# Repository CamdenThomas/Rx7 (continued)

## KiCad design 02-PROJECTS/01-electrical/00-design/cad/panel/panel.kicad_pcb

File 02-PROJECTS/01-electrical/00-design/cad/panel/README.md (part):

# Control panel — the KiCad project

*Rev 2026-10-13 (sheet and board rev 0.04, provisional - Y20, D-492) · owns: what this KiCad project
is for and what it may claim. The panel's design is `../../../data/panel_ribbon.csv`, the cavities of
`DP-DCU-E`, `dcu_channels` SN17-SN20 and parts P155, P192, P201 (D-492, D-458, D-459). Read
`../README.md` first: it is the fence.*

## Where it stands

**Rev 0.04 is the sketch's control set (D-492)**, drawn in place of Y6's board (D-380's nine keys,
four encoders and the thumbstick, superseded). It is the face of the climate unit (D-479, D-481):
the board stands 8 mm behind the faceplate, inside the unit's enclosure, the DCU carrier behind it.

- **Schematic: ERC 0 errors, 0 warnings.** `../check.py --board panel`: 79 checks, 0 mismatches
  against `panel_ribbon` (every conductor, the keys on each row and column through their diodes,
  the encoders, the spares), against `DP-DCU-E` (the plate header pin for pin) and against the
  IS31FL3236A pin table.
- **Board: DRC 0 violations, 0 unconnected, 0 schematic-parity issues** with `--severity-all`.
  180 × 84.76 mm, 2 layers, 56 footprints (52 parts and four M3 holes), 0.25 mm tracks throughout
  (0.2 mm clearance, 0.6 / 0.3 mm vias), about 1660 segments and 110 vias, a GND pour on both layers
  with solid pad connections. Routed by a script (a grid router written for this board, no
  freerouting on this machine), so it is correct, not pretty: `H-008` lays out the final board.
- No processor, no CAN node, no 12 V (D-355): the ribbon's +5 V and I²C feed the lights and the screen.
- The thumbstick, the hatch and fuel-door keys are not on this board any more: they are on the
  left plate (Y21) and reach the ribbon through `J3` (below).

## The board, as seen from the faceplate

Millimetres from the board's top-left corner, x to the right, y down. **The outline is the mock-up's,
`confirm`**: the face is 192 × 96.76 (D-481), the board the face less `PANEL_MARGIN` 6 a side
(`../climate-unit/unit_params.py`). The sketch's 180 × 60 control block is centred on the face, so
**board x = sketch x and board y = sketch y + 12.378**. Four M3 holes 4 mm in from the corners:
(4, 4), (176, 4), (4, 80.76), (176, 80.76).

| Control | Part | Board (x, y) | On the face (the sketch) |
|---|---|---|---|
| screen window | `J2` header for the module, pin 1 at (86.19, 12.0), pins along +x | window centre (90, 27.38) | 44 × 23.6 window |
| centre knob | `SW7` encoder with push | (90, 54.38) | Ø20 knob |
| fan-mode key (upper left) | `SW2` | (67.7, 48.88) | 13 × 8 cap |
| recirculate key (upper right) | `SW3` | (112.3, 48.88) | 13 × 8 cap |
| rear-defog key (lower left) | `SW1` | (67.7, 59.88) | 13 × 8 cap |
| mirror-defog key (lower right) | `SW4` | (112.3, 59.88) | 13 × 8 cap |
| driver seat knob | `SW8` | (40, 42.38) | Ø22 knob |
| passenger seat knob | `SW9` | (140, 42.38) | Ø22 knob |
| driver window switch | `SW5` | (12, 42.38) | 12 × 24 slot |
| passenger window switch | `SW6` | (168, 42.38) | 12 × 24 slot |

Key positions are the cap's centre (the `SW_PUSH_6mm` footprint's origin is pad 1, 3.25 / 2.25 mm
up-left of it). The faceplate's cut-outs are drawn on `Cmts.User`. "Upper / lower, left / right"
follow I-001: driver side is the left.

**The back** carries the rest: the ribbon header **`J1`** (2 × 13, centre (157, 68.26), pin 1 at
the right end (172.24, 69.53), toward the carrier's J4 pin 1 - `PANEL_RIBBON_Z` 16.5 above the bottom
edge, 0.5 more than the mock-up's 16 so `J3` fits under it; the carrier's J4 is straight behind at
x ≈ 158.4, this one 1.4 mm left of that so its shroud clears the board's edge, `confirm`), the plate header **`J3`** (2 × 6, centre (150, 78.6), pin 1 at the
right (156.35, 79.87)), the light driver **`U2`** at (90.05, 30.05) behind the screen with **`C2`,
`C3`, `R1`, `R2`** under it, **`C1`** by `J1` pin 26, the eight matrix diodes beside their switches,
the screen-supply jumper **`JP1`** at (101, 12) and **`TP1`** (the ribbon's spare) at (128, 80.5).

## The ribbon, J1 (`panel_ribbon`, pin for pin)

| Pin | Net | On this board |
|---|---|---|
| 1 | `+3V3` | `J3` 7 only (the stick's pots, on the plate); `JP1` 3 if the screen is set to 3.3 V |
| 2, 21, 23 | `GND` | encoder commons, the centre push, `U2`, `C1`-`C3`, `R1`, the screen; 21 / 23 guard the I²C pair |
| 3 | `ROW1` | rear defog (`D1`); `J3` 1 for the plate's hatch and fuel-door keys |
| 4 | `ROW2` | HVAC mode (`D2`), recirculate (`D3`), window DRV up (`D4`) |
| 5 | `ROW3` | window DRV down (`D5`), PASS up (`D6`), PASS down (`D7`) |
| 6 | `COL1` | rear defog, HVAC mode, window DRV down, mirror defog |
| 7 | `COL2` | recirculate, window PASS up; `J3` 2 (hatch) |
| 8 | `COL3` | window DRV up, window PASS down; `J3` 3 (fuel door) |
| 9 / 10 | `ENC_CENTRE_A` / `_B` | `SW7` A / B |
| 11 | `ENC_CENTRE_PUSH` | `SW7` S1 (S2 to GND) |
| 12 | `ROW4` | mirror defog (`D8`); columns 2 and 3 spare |
| 13 / 14 | `ENC_SEAT_DRV_A` / `_B` | `SW8` A / B |
| 15 / 16 | `ENC_SEAT_PASS_A` / `_B` | `SW9` A / B |
| 17 / 18 / 19 | `JOY_X` / `JOY_Y` / `JOY_PRESS` | `J3` 4 / 5 / 6 only |
| 20 | `AGND` | `J3` 8 only - kept apart from `GND` on this board; they meet on the carrier |
| 22 / 24 | `PNL_SDA` / `PNL_SCL` | `U2`, the screen `J2`, `J3` 9 / 10 |
| 25 | `SPARE` | `TP1` |
| 26 | `+5V_PNL` | `U2` VCC, the 24 LED anodes, `C1`-`C3`, `R2`, `JP1` 1, `J3` 12 |

**The matrix:** one 1N4148W per key, cathode to the row, anode toward the column (a row driven low
pulls its column low; with every row held low any press wakes the DCU). Eight diodes on this board,
the plate's two keys carry their own (D-492).

**The window switches** are drawn as a centre-sprung **DPDT** (ON)-OFF-(ON) toggle, one pole per
direction. The record puts DRV up at `ROW2` / `COL3` and DRV down at `ROW3` / `COL1`: two different
rows *and* two different columns, which an SPDT's single common cannot serve without a phantom key
(its common would join two rows or two columns). With two poles each contact is an ordinary key
behind its own diode. PASS (both on `ROW3`) could use an SPDT, but both switches are the same part.
If the record re-pins DRV up / down onto one row or one column, an SPDT fits and P155 can stay as worded.

## The plate header, J3 - what the left plate (Y21) carries

`J3` is `DP-DCU-E` 1-12 pin for pin; a lead joins it to the upper connector board's `J8`, which runs
straight through to the DT13 `DP-DCU-E` in the unit's back wall and on to the plate's cable (P200).

| Pin | Net | panel_ribbon | On the plate |
|---|---|---|---|
| 1 | `ROW1` | 3 | the row for its two keys |
| 2 | `COL2` | 7 | the hatch key, through its own 1N4148W |
| 3 | `COL3` | 8 | the fuel-door key, through its own 1N4148W |
| 4 / 5 | `JOY_X` / `JOY_Y` | 17 / 18 | the mirror stick's wipers (P156) |
| 6 | `JOY_PRESS` | 19 | the stick's push, to GND |
| 7 | `+3V3` | 1 | the stick's pot supply |
| 8 | `AGND` | 20 | the stick's pot ground |
| 9 / 10 | `PNL_SDA` / `PNL_SCL` | 22 / 24 | the plate's own I²C LED driver (its symbols) |
| 11 | `GND` | 21 | the plate's lights and logic return |
| 12 | `+5V_PNL` | 26 | the plate's LED supply |

The two wink switches on the plate are not here: they stay hardwired to the PMU (DV24, D-492).

## The lights (D-458, D-492)

**`U2`, IS31FL3236A-TQLS4** (eTQFP-48, I²C **0x3C**, AD to GND), as on Y6: `C1` 10 µF at `J1` 26,
`C2` 1 µF and `C3` 100 nF at VCC, `R1` 10 k on R_EXT (IMAX = 58.5 × 1.3 V / 10 k = 7.6 mA a channel,
p.11), `R2` 100 k holding SDB high (on and blank until written). 24 LEDs, 0603, anode on `+5V_PNL`,
cathode to the channel - 24 × 7.6 mA = 0.18 A at full current. The fan and temperature arcs of D-458
are gone; the screen shows those. Which lights follow the headlights (the ring, the window and seat
symbols) and which show state (the key symbols, the seat arcs) is firmware's (I-004), not wiring.

The channel map was chosen from the geometry (channels taken round `U2` in the same order as the
LEDs around it, so the runs do not cross); the record names no order. **F-018 reads it from here.**

| OUT | LED | What it lights | x | y |
|---|---|---|---|---|
| 3 | `LED8` | knob ring, lower left | 80.454 | 63.924 |
| 5 | `LED1` | rear-defog key symbol | 73.3 | 59.878 |
| 6 | `LED5` | knob ring, upper left | 80.454 | 44.832 |
| 7 | `LED2` | fan-mode key symbol | 73.3 | 48.878 |
| 9 | `LED18` | driver seat heat 3 | 54.943 | 43.685 |
| 10 | `LED13` | driver seat cool 3 | 25.057 | 43.685 |
| 11 | `LED17` | driver seat heat 2 | 54.095 | 37.248 |
| 13 | `LED14` | driver seat cool 2 | 25.905 | 37.248 |
| 14 | `LED16` | driver seat heat 1 | 50.607 | 31.771 |
| 15 | `LED9` | driver window symbol | 12.0 | 32.978 |
| 17 | `LED15` | driver seat cool 1 | 29.393 | 31.771 |
| 18 | `LED11` | driver seat symbol | 40.0 | 27.978 |
| 19 | `LED12` | passenger seat symbol | 140.0 | 27.978 |
| 21 | `LED22` | passenger seat heat 1 | 150.607 | 31.771 |
| 22 | `LED10` | passenger window symbol | 168.0 | 32.978 |
| 23 | `LED21` | passenger seat cool 1 | 129.393 | 31.771 |
| 25 | `LED23` | passenger seat heat 2 | 154.095 | 37.248 |
| 26 | `LED20` | passenger seat cool 2 | 125.905 | 37.248 |
| 27 | `LED24` | passenger seat heat 3 | 154.943 | 43.685 |
| 29 | `LED19` | passenger seat cool 3 | 125.057 | 43.685 |
| 30 | `LED3` | recirculate key symbol | 106.7 | 48.878 |
| 31 | `LED6` | knob ring, upper right | 99.546 | 44.832 |
| 33 | `LED4` | mirror-defog key symbol | 106.7 | 59.878 |
| 34 | `LED7` | knob ring, lower right | 99.546 | 63.924 |

OUT 1, 2, 4, 8, 12, 16, 20, 24, 28, 32, 35 and 36 are open. The (x, y) are the faceplate's windows
for LP20, from the board's top-left as seen from the face.

- **Key symbols** sit inside the 13 × 8 cap, beside the tactile switch on the knob's side (5.6 mm from
  the cap's centre; the switch fills the middle), lit through the cap (D-488).
- **The knob's ring:** four LEDs on the diagonals, 13.5 mm from the shaft, toward the four keys (I-001).
- **Seat arcs:** 15 mm from the shaft, OFF at the top (D-073); cool 3-2-1 anticlockwise at −95°, −70°,
  −45° (blue), heat 1-2-3 clockwise at +45°, +70°, +95° (red), the same on both knobs.
- **Window symbols** 9.4 mm above the switch, inside its 12 × 24 slot; **seat symbols** 14.4 mm above
  the knob's shaft. I-005 asks for the window symbol on the switch's cap and the seat symbol in the
  knob's centre: both are part questions (below), so the LED sits beside the control for now.

## The screen (P201)

`J2` is a placeholder for a 128 × 64-class I²C module's own 4-pin header, in the common order
**GND, VCC, SCL, SDA**, centred over the window's top edge (a 1.3-inch module's header sits there).
**`JP1` picks its supply and is left open**: bridge 1-2 for `+5V_PNL` (what the record allows - its
`+3V3` line says "nothing else on the panel is powered from it"), or 2-3 for `+3V3`. Many modules pull
SDA / SCL up to their VCC pin: such a module at 5 V would pull the DCU's 3.3 V bus to 5 V, which the
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
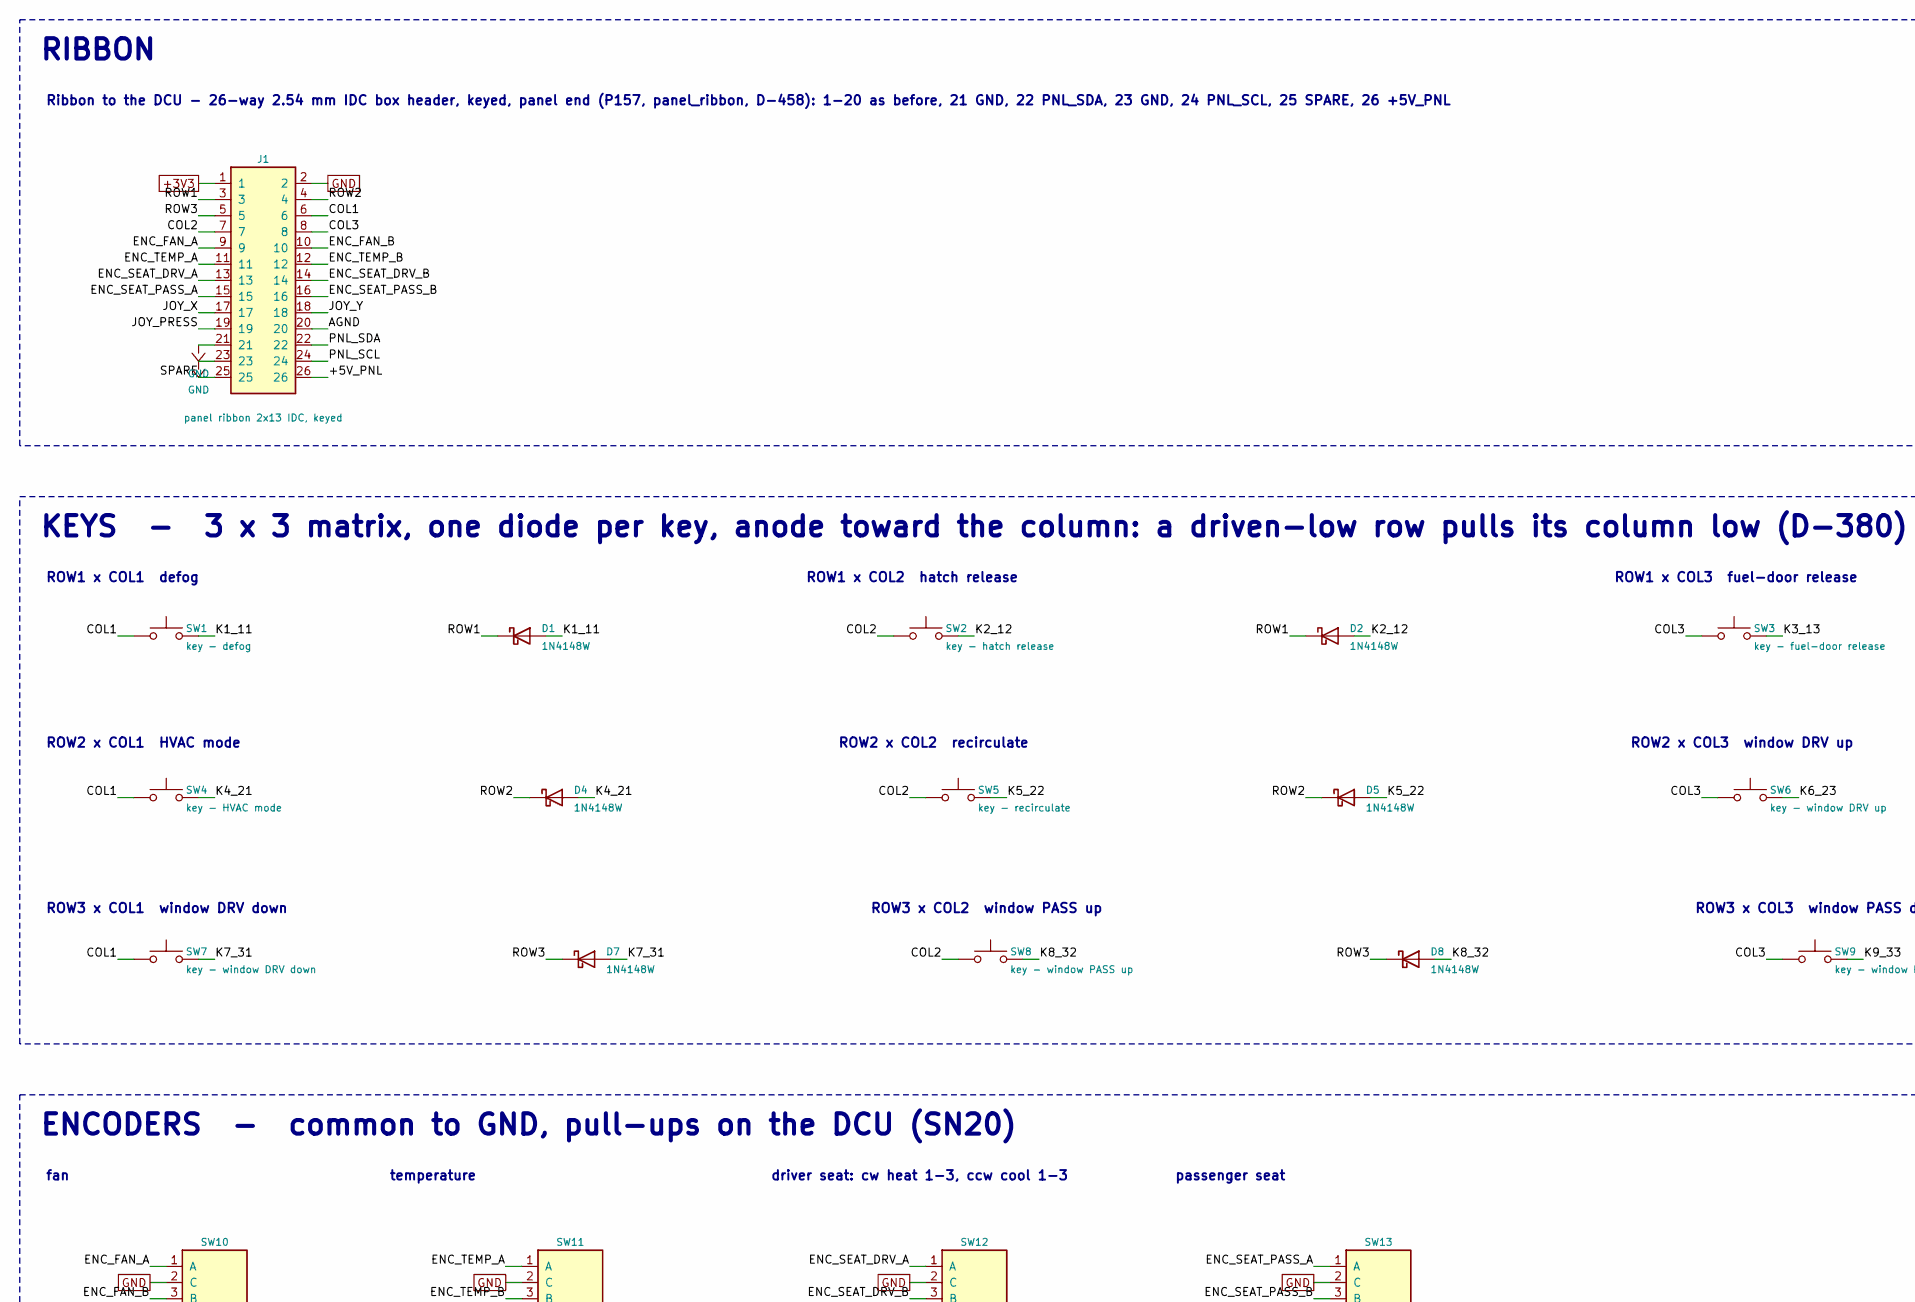
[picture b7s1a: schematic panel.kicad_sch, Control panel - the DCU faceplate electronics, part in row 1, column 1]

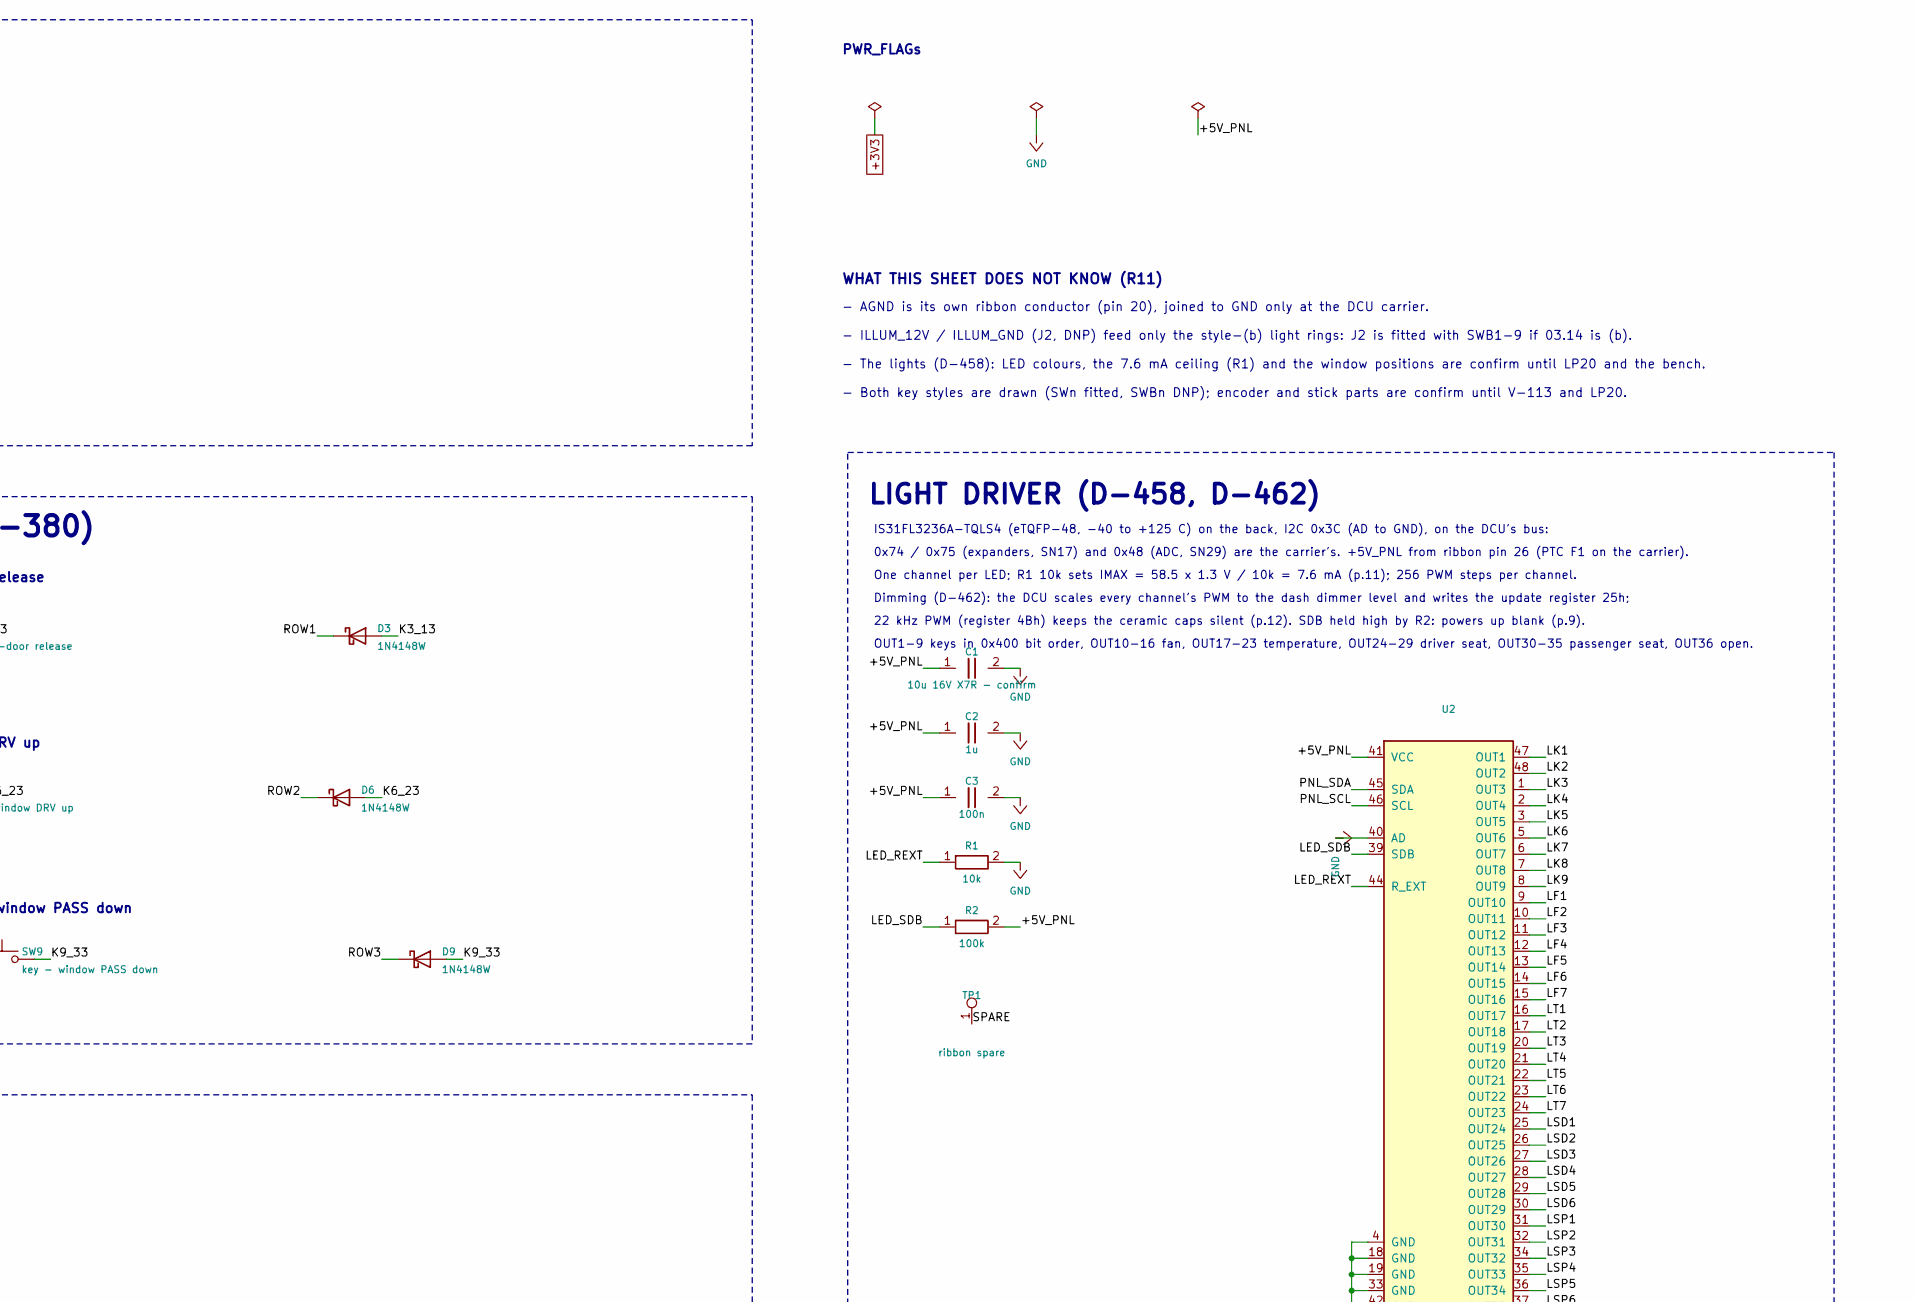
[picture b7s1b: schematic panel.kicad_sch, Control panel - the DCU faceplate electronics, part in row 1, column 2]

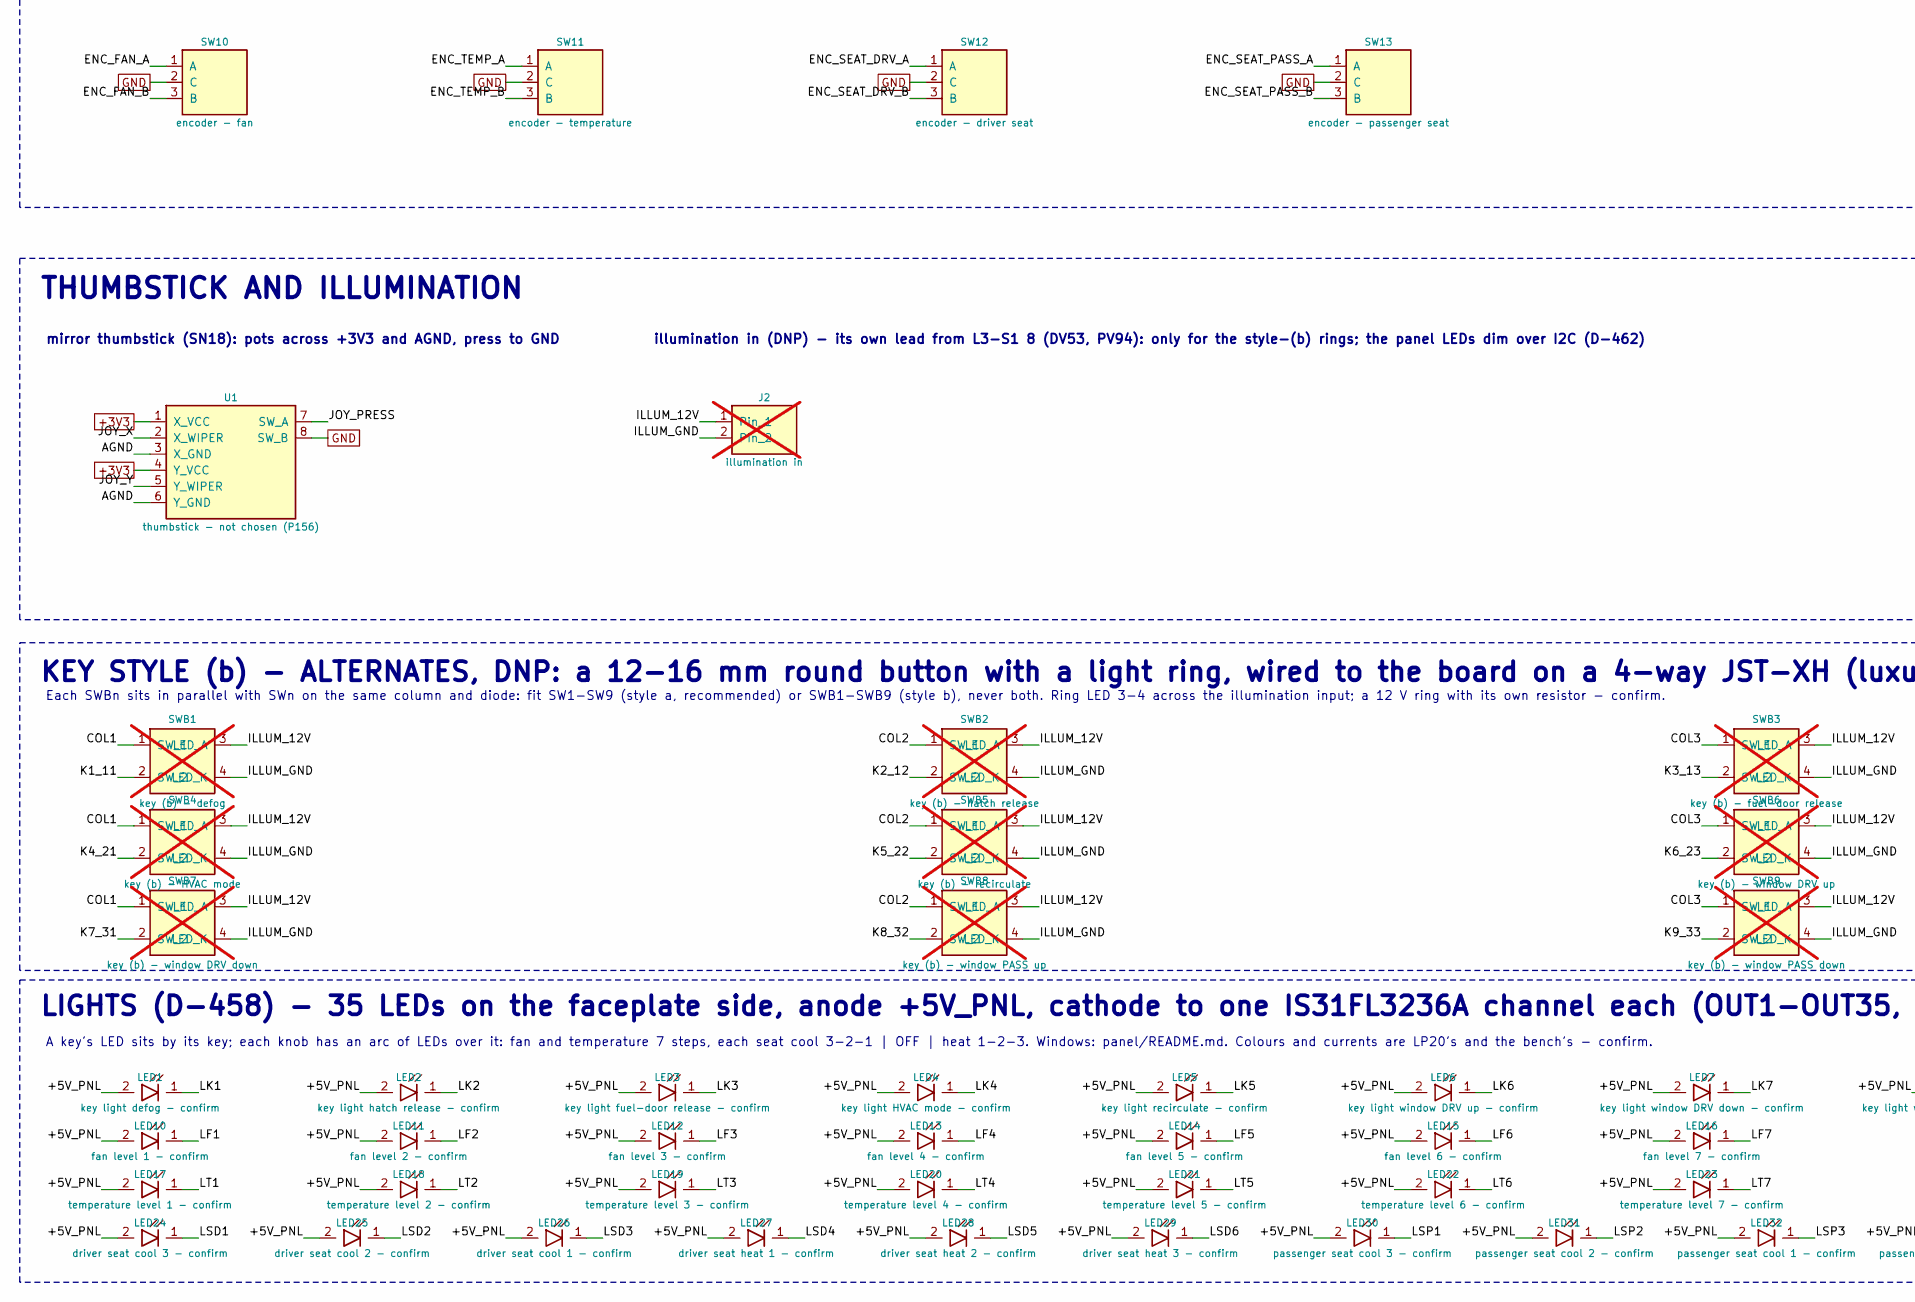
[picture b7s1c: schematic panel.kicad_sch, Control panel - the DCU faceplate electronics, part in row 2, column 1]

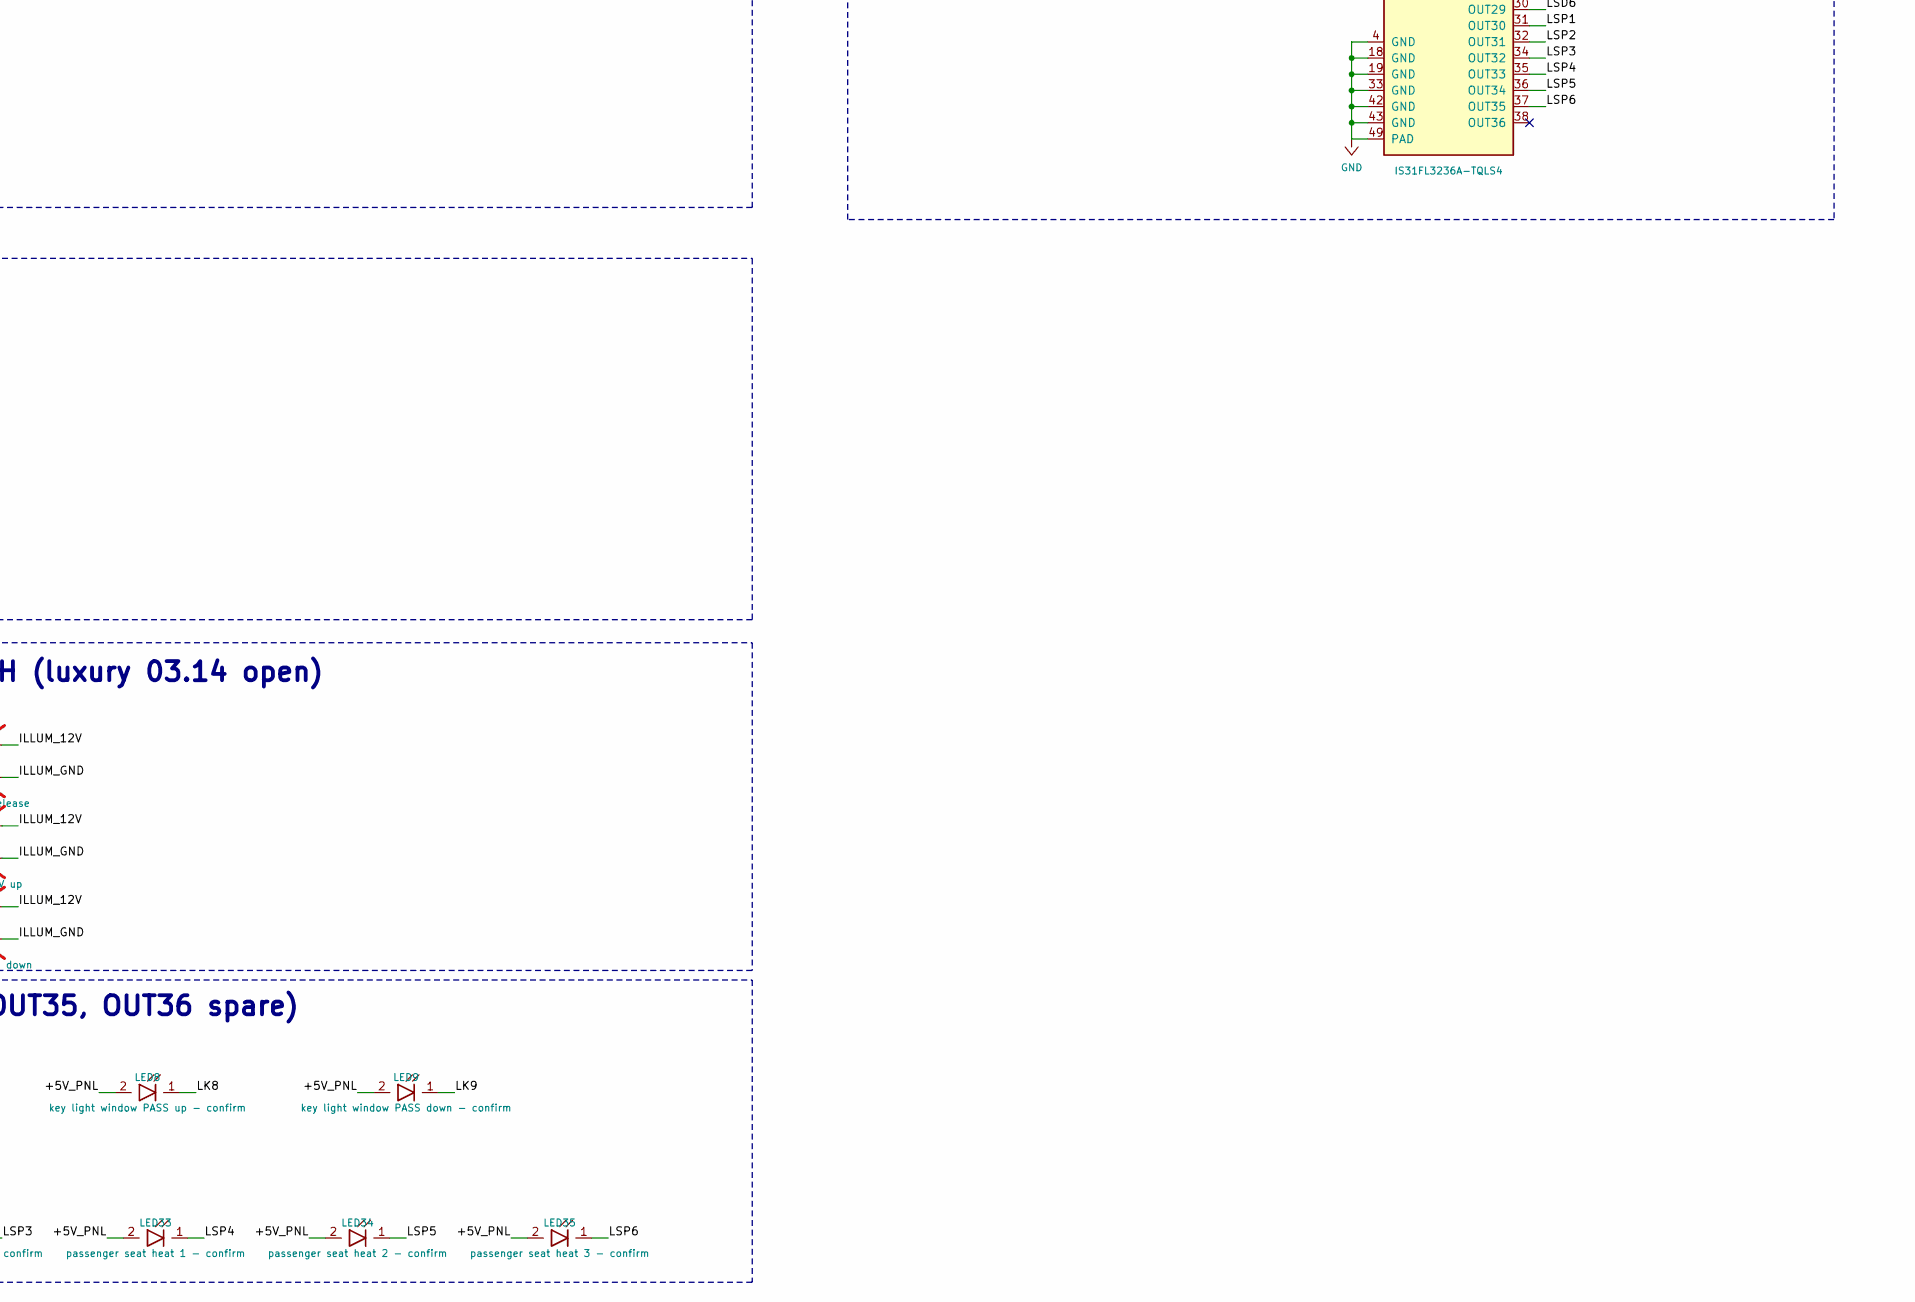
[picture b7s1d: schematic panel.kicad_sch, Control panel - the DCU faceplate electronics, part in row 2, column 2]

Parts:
C1: 10u 16V X7R - confirm; C_0805_2012Metric
C2: 1u; C_0603_1608Metric
C3: 100n; C_0603_1608Metric
D1, D2, D3, D4, D5, D6, D7, D8, D9: 1N4148W; D_SOD-123
J1: panel ribbon 2x13 IDC, keyed; IDC-Header_2x13_P2.54mm_Vertical
J2: illumination in; JST_XH_B2B-XH-A_1x02_P2.50mm_Vertical; not fitted
LED1: key light defog - confirm; LED_1206_3216Metric
LED2: key light hatch release - confirm; LED_1206_3216Metric
LED3: key light fuel-door release - confirm; LED_1206_3216Metric
LED4: key light HVAC mode - confirm; LED_1206_3216Metric
LED5: key light recirculate - confirm; LED_1206_3216Metric
LED6: key light window DRV up - confirm; LED_1206_3216Metric
LED7: key light window DRV down - confirm; LED_1206_3216Metric
LED8: key light window PASS up - confirm; LED_1206_3216Metric
LED9: key light window PASS down - confirm; LED_1206_3216Metric
LED10: fan level 1 - confirm; LED_0603_1608Metric
LED11: fan level 2 - confirm; LED_0603_1608Metric
LED12: fan level 3 - confirm; LED_0603_1608Metric
LED13: fan level 4 - confirm; LED_0603_1608Metric
LED14: fan level 5 - confirm; LED_0603_1608Metric
LED15: fan level 6 - confirm; LED_0603_1608Metric
LED16: fan level 7 - confirm; LED_0603_1608Metric
LED17: temperature level 1 - confirm; LED_0603_1608Metric
LED18: temperature level 2 - confirm; LED_0603_1608Metric
LED19: temperature level 3 - confirm; LED_0603_1608Metric
LED20: temperature level 4 - confirm; LED_0603_1608Metric
LED21: temperature level 5 - confirm; LED_0603_1608Metric
LED22: temperature level 6 - confirm; LED_0603_1608Metric
LED23: temperature level 7 - confirm; LED_0603_1608Metric
LED24: driver seat cool 3 - confirm; LED_0603_1608Metric
LED25: driver seat cool 2 - confirm; LED_0603_1608Metric
LED26: driver seat cool 1 - confirm; LED_0603_1608Metric
LED27: driver seat heat 1 - confirm; LED_0603_1608Metric
LED28: driver seat heat 2 - confirm; LED_0603_1608Metric
LED29: driver seat heat 3 - confirm; LED_0603_1608Metric
LED30: passenger seat cool 3 - confirm; LED_0603_1608Metric
LED31: passenger seat cool 2 - confirm; LED_0603_1608Metric
LED32: passenger seat cool 1 - confirm; LED_0603_1608Metric
LED33: passenger seat heat 1 - confirm; LED_0603_1608Metric
LED34: passenger seat heat 2 - confirm; LED_0603_1608Metric
LED35: passenger seat heat 3 - confirm; LED_0603_1608Metric
R1: 10k; R_0603_1608Metric
R2: 100k; R_0603_1608Metric
SW1: key - defog; SW_PUSH_6mm_H13mm
SW2: key - hatch release; SW_PUSH_6mm_H13mm
SW3: key - fuel-door release; SW_PUSH_6mm_H13mm
SW4: key - HVAC mode; SW_PUSH_6mm_H13mm
SW5: key - recirculate; SW_PUSH_6mm_H13mm
SW6: key - window DRV up; SW_PUSH_6mm_H13mm
SW7: key - window DRV down; SW_PUSH_6mm_H13mm
SW8: key - window PASS up; SW_PUSH_6mm_H13mm
SW9: key - window PASS down; SW_PUSH_6mm_H13mm
SW10: encoder - fan; RotaryEncoder_Bourns_Vertical_PEC11R-4xxxF-Sxxxx
SW11: encoder - temperature; RotaryEncoder_Bourns_Vertical_PEC11R-4xxxF-Sxxxx
SW12: encoder - driver seat; RotaryEncoder_Bourns_Vertical_PEC11R-4xxxF-Sxxxx
SW13: encoder - passenger seat; RotaryEncoder_Bourns_Vertical_PEC11R-4xxxF-Sxxxx
SWB1: key (b) - defog; JST_XH_B4B-XH-A_1x04_P2.50mm_Vertical; not fitted
SWB2: key (b) - hatch release; JST_XH_B4B-XH-A_1x04_P2.50mm_Vertical; not fitted
SWB3: key (b) - fuel-door release; JST_XH_B4B-XH-A_1x04_P2.50mm_Vertical; not fitted
SWB4: key (b) - HVAC mode; JST_XH_B4B-XH-A_1x04_P2.50mm_Vertical; not fitted
SWB5: key (b) - recirculate; JST_XH_B4B-XH-A_1x04_P2.50mm_Vertical; not fitted
SWB6: key (b) - window DRV up; JST_XH_B4B-XH-A_1x04_P2.50mm_Vertical; not fitted
SWB7: key (b) - window DRV down; JST_XH_B4B-XH-A_1x04_P2.50mm_Vertical; not fitted
SWB8: key (b) - window PASS up; JST_XH_B4B-XH-A_1x04_P2.50mm_Vertical; not fitted
SWB9: key (b) - window PASS down; JST_XH_B4B-XH-A_1x04_P2.50mm_Vertical; not fitted
TP1: ribbon spare; TestPoint_Pad_D1.5mm
U1: thumbstick - not chosen (P156); Thumbstick_P156_Placeholder_2x04_P2.54mm
U2: IS31FL3236A-TQLS4; TQFP-48-1EP_7x7mm_P0.5mm_EP4.11x4.11mm

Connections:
+3V3: J1.1, U1.1 (X_VCC), U1.4 (Y_VCC)
/+5V_PNL: C1.1, C2.1, C3.1, J1.26, LED1.2 (A), LED2.2 (A), LED3.2 (A), LED4.2 (A), LED5.2 (A), LED6.2 (A), LED7.2 (A), LED8.2 (A), LED9.2 (A), LED10.2 (A), LED11.2 (A), LED12.2 (A), LED13.2 (A), LED14.2 (A), LED15.2 (A), LED16.2 (A), LED17.2 (A), LED18.2 (A), LED19.2 (A), LED20.2 (A), LED21.2 (A), LED22.2 (A), LED23.2 (A), LED24.2 (A), LED25.2 (A), LED26.2 (A), LED27.2 (A), LED28.2 (A), LED29.2 (A), LED30.2 (A), LED31.2 (A), LED32.2 (A), LED33.2 (A), LED34.2 (A), LED35.2 (A), R2.2, U2.41 (VCC)
/AGND: J1.20, U1.3 (X_GND), U1.6 (Y_GND)
/COL1: J1.6, SW1.1, SW4.1, SW7.1, SWB1.1 (SW_1), SWB4.1 (SW_1), SWB7.1 (SW_1)
/COL2: J1.7, SW2.1, SW5.1, SW8.1, SWB2.1 (SW_1), SWB5.1 (SW_1), SWB8.1 (SW_1)
/COL3: J1.8, SW3.1, SW6.1, SW9.1, SWB3.1 (SW_1), SWB6.1 (SW_1), SWB9.1 (SW_1)
/ENC_FAN_A: J1.9, SW10.1 (A)
/ENC_FAN_B: J1.10, SW10.3 (B)
/ENC_SEAT_DRV_A: J1.13, SW12.1 (A)
/ENC_SEAT_DRV_B: J1.14, SW12.3 (B)
/ENC_SEAT_PASS_A: J1.15, SW13.1 (A)
/ENC_SEAT_PASS_B: J1.16, SW13.3 (B)
/ENC_TEMP_A: J1.11, SW11.1 (A)
/ENC_TEMP_B: J1.12, SW11.3 (B)
/ILLUM_12V: J2.1, SWB1.3 (LED_A), SWB2.3 (LED_A), SWB3.3 (LED_A), SWB4.3 (LED_A), SWB5.3 (LED_A), SWB6.3 (LED_A), SWB7.3 (LED_A), SWB8.3 (LED_A), SWB9.3 (LED_A)
/ILLUM_GND: J2.2, SWB1.4 (LED_K), SWB2.4 (LED_K), SWB3.4 (LED_K), SWB4.4 (LED_K), SWB5.4 (LED_K), SWB6.4 (LED_K), SWB7.4 (LED_K), SWB8.4 (LED_K), SWB9.4 (LED_K)
/JOY_PRESS: J1.19, U1.7 (SW_A)
/JOY_X: J1.17, U1.2 (X_WIPER)
/JOY_Y: J1.18, U1.5 (Y_WIPER)
/K1_11: D1.2 (A), SW1.2, SWB1.2 (SW_2)
/K2_12: D2.2 (A), SW2.2, SWB2.2 (SW_2)
/K3_13: D3.2 (A), SW3.2, SWB3.2 (SW_2)
/K4_21: D4.2 (A), SW4.2, SWB4.2 (SW_2)
/K5_22: D5.2 (A), SW5.2, SWB5.2 (SW_2)
/K6_23: D6.2 (A), SW6.2, SWB6.2 (SW_2)
/K7_31: D7.2 (A), SW7.2, SWB7.2 (SW_2)
/K8_32: D8.2 (A), SW8.2, SWB8.2 (SW_2)
/K9_33: D9.2 (A), SW9.2, SWB9.2 (SW_2)
/LED_REXT: R1.1, U2.44 (R_EXT)
/LED_SDB: R2.1, U2.39 (SDB)
/LF1: LED10.1 (K), U2.9 (OUT10)
/LF2: LED11.1 (K), U2.10 (OUT11)
/LF3: LED12.1 (K), U2.11 (OUT12)
/LF4: LED13.1 (K), U2.12 (OUT13)
/LF5: LED14.1 (K), U2.13 (OUT14)
/LF6: LED15.1 (K), U2.14 (OUT15)
/LF7: LED16.1 (K), U2.15 (OUT16)
/LK1: LED1.1 (K), U2.47 (OUT1)
/LK2: LED2.1 (K), U2.48 (OUT2)
/LK3: LED3.1 (K), U2.1 (OUT3)
/LK4: LED4.1 (K), U2.2 (OUT4)
/LK5: LED5.1 (K), U2.3 (OUT5)
/LK6: LED6.1 (K), U2.5 (OUT6)
/LK7: LED7.1 (K), U2.6 (OUT7)
/LK8: LED8.1 (K), U2.7 (OUT8)
/LK9: LED9.1 (K), U2.8 (OUT9)
/LSD1: LED24.1 (K), U2.25 (OUT24)
/LSD2: LED25.1 (K), U2.26 (OUT25)
/LSD3: LED26.1 (K), U2.27 (OUT26)
/LSD4: LED27.1 (K), U2.28 (OUT27)
/LSD5: LED28.1 (K), U2.29 (OUT28)
/LSD6: LED29.1 (K), U2.30 (OUT29)
/LSP1: LED30.1 (K), U2.31 (OUT30)
/LSP2: LED31.1 (K), U2.32 (OUT31)
/LSP3: LED32.1 (K), U2.34 (OUT32)
/LSP4: LED33.1 (K), U2.35 (OUT33)
/LSP5: LED34.1 (K), U2.36 (OUT34)
/LSP6: LED35.1 (K), U2.37 (OUT35)
/LT1: LED17.1 (K), U2.16 (OUT17)
/LT2: LED18.1 (K), U2.17 (OUT18)
/LT3: LED19.1 (K), U2.20 (OUT19)
/LT4: LED20.1 (K), U2.21 (OUT20)
/LT5: LED21.1 (K), U2.22 (OUT21)
/LT6: LED22.1 (K), U2.23 (OUT22)
/LT7: LED23.1 (K), U2.24 (OUT23)
/PNL_SCL: J1.24, U2.46 (SCL)
/PNL_SDA: J1.22, U2.45 (SDA)
/ROW1: D1.1 (K), D2.1 (K), D3.1 (K), J1.3
/ROW2: D4.1 (K), D5.1 (K), D6.1 (K), J1.4
/ROW3: D7.1 (K), D8.1 (K), D9.1 (K), J1.5
/SPARE: J1.25, TP1.1
GND: C1.2, C2.2, C3.2, J1.2, J1.21, J1.23, R1.2, SW10.2 (C), SW11.2 (C), SW12.2 (C), SW13.2 (C), U1.8 (SW_B), U2.4 (GND), U2.18 (GND), U2.19 (GND), U2.33 (GND), U2.40 (AD), U2.42 (GND), U2.43 (GND), U2.49 (PAD)

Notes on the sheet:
RIBBON
Ribbon to the DCU - 26-way 2.54 mm IDC box header, keyed, panel end (P157, panel_ribbon, D-458): 1-20 as before, 21 GND, 22 PNL_SDA, 23 GND, 24 PNL_SCL, 25 SPARE, 26 +5V_PNL
KEYS - 3 x 3 matrix, one diode per key, anode toward the column: a driven-low row pulls its column low (D-380)
ROW1 x COL1 defog
ROW1 x COL2 hatch release
ROW1 x COL3 fuel-door release
ROW2 x COL1 HVAC mode
ROW2 x COL2 recirculate
ROW2 x COL3 window DRV up
ROW3 x COL1 window DRV down
ROW3 x COL2 window PASS up
ROW3 x COL3 window PASS down
ENCODERS - common to GND, pull-ups on the DCU (SN20)
fan
temperature
driver seat: cw heat 1-3, ccw cool 1-3
passenger seat
THUMBSTICK AND ILLUMINATION
mirror thumbstick (SN18): pots across +3V3 and AGND, press to GND
illumination in (DNP) - its own lead from L3-S1 8 (DV53, PV94): only for the style-(b) rings; the panel LEDs dim over I2C (D-462)
PWR_FLAGs
WHAT THIS SHEET DOES NOT KNOW (R11)
- AGND is its own ribbon conductor (pin 20), joined to GND only at the DCU carrier.
- ILLUM_12V / ILLUM_GND (J2, DNP) feed only the style-(b) light rings: J2 is fitted with SWB1-9 if 03.14 is (b).
- The lights (D-458): LED colours, the 7.6 mA ceiling (R1) and the window positions are confirm until LP20 and the bench.
- Both key styles are drawn (SWn fitted, SWBn DNP); encoder and stick parts are confirm until V-113 and LP20.
KEY STYLE (b) - ALTERNATES, DNP: a 12-16 mm round button with a light ring, wired to the board on a 4-way JST-XH (luxury 03.14 open)
Each SWBn sits in parallel with SWn on the same column and diode: fit SW1-SW9 (style a, recommended) or SWB1-SWB9 (style b), never both. Ring LED 3-4 across the illumination input; a 12 V ring with its own resistor - confirm.
LIGHTS (D-458) - 35 LEDs on the faceplate side, anode +5V_PNL, cathode to one IS31FL3236A channel each (OUT1-OUT35, OUT36 spare)
A key's LED sits by its key; each knob has an arc of LEDs over it: fan and temperature 7 steps, each seat cool 3-2-1 | OFF | heat 1-2-3. Windows: panel/README.md. Colours and currents are LP20's and the bench's - confirm.
LIGHT DRIVER (D-458, D-462)
IS31FL3236A-TQLS4 (eTQFP-48, -40 to +125 C) on the back, I2C 0x3C (AD to GND), on the DCU's bus:
0x74 / 0x75 (expanders, SN17) and 0x48 (ADC, SN29) are the carrier's. +5V_PNL from ribbon pin 26 (PTC F1 on the carrier).
One channel per LED; R1 10k sets IMAX = 58.5 x 1.3 V / 10k = 7.6 mA (p.11); 256 PWM steps per channel.
Dimming (D-462): the DCU scales every channel's PWM to the dash dimmer level and writes the update register 25h;
22 kHz PWM (register 4Bh) keeps the ceramic caps silent (p.12). SDB held high by R2: powers up blank (p.9).
OUT1-9 keys in 0x400 bit order, OUT10-16 fan, OUT17-23 temperature, OUT24-29 driver seat, OUT30-35 passenger seat, OUT36 open.

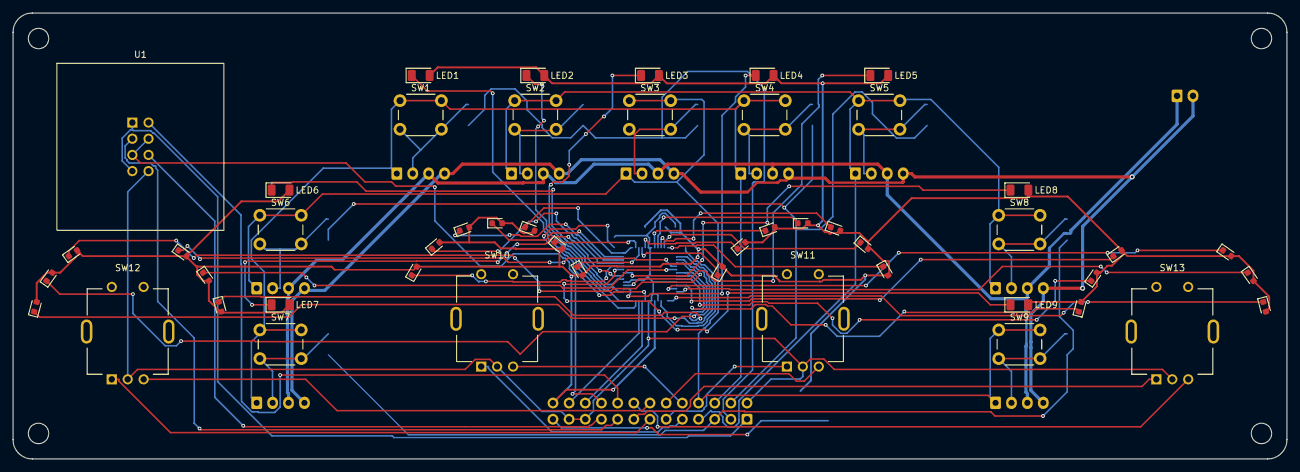
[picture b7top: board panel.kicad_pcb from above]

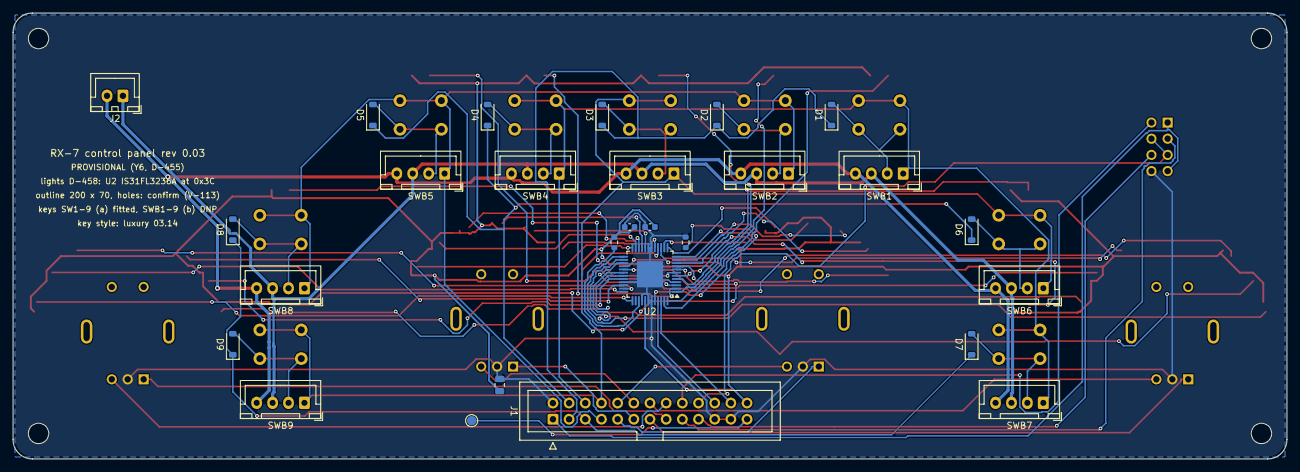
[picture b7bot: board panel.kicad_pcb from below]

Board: 2 copper layers, 200.0 x 70.0 mm, 80 parts (27 on the bottom side), 72 nets.

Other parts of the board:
H1, H2, H3, H4: M3 - confirm against V-113 / LP20; MountingHole_3.2mm_M3

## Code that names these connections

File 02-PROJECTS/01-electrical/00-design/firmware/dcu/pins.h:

/*
 * pins.h — the DCU carrier's pin map: Teensy 4.1 edge pins and the
 * TCA9539-Q1 expander's ports (H-002, D-452)
 *
 * Owns (R6), from 02-PROJECTS/01-electrical/data:
 *   dcu_channels.teensy_pin   every number below, channel by channel
 *   panel_ribbon              which ribbon conductor each panel pin reads
 * The sheet (cad/dcu-carrier, checked against the same rows by cad/check.py)
 * is drawn from the same column, so a pin moved in the record moves here.
 *
 * No Arduino headers: tests/test_dcu.cpp includes this file and checks the
 * map (every edge pin 0-41 used once, nothing on the bottom pads 48-54, the
 * centre encoder on 40 / 41 with its push on 34, ROW4 on 35, I2C on 18 / 19;
 * D-492 re-reads the same pins, the carrier does not change). Analog inputs are given by pin
 * number (14 = A0), which Teensy's analogRead() takes as it is.
 */

#ifndef DCU_PINS_H
#define DCU_PINS_H

#include <stdint.h>

/* ------------------------- Teensy edge pins ------------------------- */
/* SN26: CAN2 is 0 CRX2 / 1 CTX2, ACAN_T4's can2 default - not set here.  */
#define PIN_CAN_RX          0
#define PIN_CAN_TX          1
static const int PIN_SERVO[3]   = { 2, 3, 4 };       /* SN15 mode · blend · recirc (climate.h order) */
static const int PIN_COMFORT[5] = { 5, 6, 7, 8, 9 }; /* SN16 seat heat DRV · PASS, seat cool DRV · PASS
                                                      * (BTS3011TE low side) · mirror heat IN (BTT6050) */
static const int PIN_BLOWER      = 10;               /* SN14, PWM 25 kHz, own timer */
static const int PIN_WAKE        = 11;               /* SN21, NPN into a 12 V PMOS -> DP-DCU 6 */
static const int PIN_EXP_INT     = 12;               /* SN17, TCA9539 INT, open drain, pulled up */
static const int PIN_EXP_RESET   = 13;               /* SN17, TCA9539 RESET, active low, pulled down
                                                      * (also the Teensy's LED: it lights while released) */
static const int PIN_CABIN_NTC   = 14;               /* SN11, A0 */
static const int PIN_OAT_NTC     = 15;               /* SN12, A1 */
static const int PIN_CURRENT     = 16;               /* SN13, A2 */
static const int PIN_JOY_PRESS   = 17;               /* SN18, ribbon 19 */
static const int PIN_I2C_SDA     = 18;               /* Wire, to the TCA9539 (D-452) */
static const int PIN_I2C_SCL     = 19;
static const int PIN_JOY_X       = 20;               /* SN18, A6, ribbon 17 */
static const int PIN_JOY_Y       = 21;               /* SN18, A7, ribbon 18 */
static const int PIN_WIN[4]      = { 22, 23, 24, 25 }; /* SN22 BTT6200 IN0-3: DRV up, DRV down, PASS up,
                                                        * PASS down -> DP-DCU-B 1-4 */
static const int PIN_REL_HATCH   = 26;               /* SN23, K3 85 via DP-DCU-B 10 */
static const int PIN_REL_FUEL    = 27;               /* SN23, K4 85 via DP-DCU-B 11. Each drives a
                                                      * PMV37ENEA gate with a pull-down on the board
                                                      * (D-465): a reset or a floating pin cannot
                                                      * select. K3 / K4's 86 is live whenever O10
                                                      * is, so HIGH alone fires the solenoid with
                                                      * the key on - panel.h's release_step refuses
                                                      * unless stopped and drops it after 1.5 s */
static const int PIN_ROW[4]      = { 28, 29, 30, 35 }; /* SN19, ribbon 3-5 and 12: ROW4 on 35 (D-492,
                                                        * was the temperature encoder's B) */
static const int PIN_COL[3]      = { 31, 32, 33 };   /* SN19, ribbon 6-8 */
enum { ENC_CENTRE = 0, ENC_SEAT_DRV, ENC_SEAT_PASS, ENC_COUNT };
static const int PIN_ENC_A[ENC_COUNT] = { 40, 36, 38 };   /* SN20, ribbon 9, 13, 15 */
static const int PIN_ENC_B[ENC_COUNT] = { 41, 37, 39 };   /* SN20, ribbon 10, 14, 16 - the centre
                                                           * knob is the old fan encoder's pins,
                                                           * moved off 18 / 19 by D-452 */
static const int PIN_CENTRE_PUSH = 34;               /* SN20, ribbon 11: the centre knob's push to GND
                                                      * (D-492, was the temperature encoder's A) */

/* ------------------------- TCA9539-Q1 ports (U12) -------------------------
 * Bit n of the 16-bit word is port P0n for n < 8 and P1(n-8) above. The
 * order is dcu_channels': SN17 "P00-P05 IN1/EN1-IN3/EN3, P06 EN4, P07
 * nSLEEP, P10 nFAULT", SN22 "DEN, DSEL0, DSEL1 on P11-P13", SN16 "mirror heat
 * DEN on P14", SN26 "STB on P15", SN24 "power-good on P16". DRV8962 channel
 * 1 is the motor common, 2 the left motor, 3 the right, 4 the clutch sink
 * (D-360; the sheet's OUT1-4 to DP-DCU-B 5-8).                           */
#define EXP_P(port, bit)   ((uint16_t)(1u << ((port) * 8 + (bit))))
#define EXP_MIR_IN1        EXP_P(0, 0)   /* common  - high or low   */
#define EXP_MIR_EN1        EXP_P(0, 1)   /*           off = open    */
#define EXP_MIR_IN2        EXP_P(0, 2)   /* left    */
#define EXP_MIR_EN2        EXP_P(0, 3)
#define EXP_MIR_IN3        EXP_P(0, 4)   /* right   */
#define EXP_MIR_EN3        EXP_P(0, 5)
#define EXP_MIR_EN4        EXP_P(0, 6)   /* clutch: IN4 tied low, EN4 on = low FET sinks the coils */
#define EXP_MIR_NSLEEP     EXP_P(0, 7)   /* low = asleep; R35 holds it low through a reset */
#define EXP_MIR_NFAULT     EXP_P(1, 0)   /* input, low = fault (R36 pull-up) */
#define EXP_WIN_DEN        EXP_P(1, 1)   /* BTT6200 diagnosis enable - IS is unread (D-452) */
#define EXP_WIN_DSEL0      EXP_P(1, 2)
#define EXP_WIN_DSEL1      EXP_P(1, 3)
#define EXP_MH_DEN         EXP_P(1, 4)   /* BTT6050 diagnosis enable - IS unread */
#define EXP_CAN_STB        EXP_P(1, 5)   /* TCAN1042 STB: low = normal; R8 holds it low through a reset */
#define EXP_PG_5V          EXP_P(1, 6)   /* input, the logic buck's power-good */
#define EXP_P17            EXP_P(1, 7)   /* input. D-452 calls it spare; the sheet wires the four
                                          * BTS3011TE STATUS pins to it (SEAT_STATUS) - read, not
                                          * acted on, until the record names it (confirm) */

#define EXP_INPUTS   ((uint16_t)(EXP_MIR_NFAULT | EXP_PG_5V | EXP_P17))
#define EXP_OUTPUTS  ((uint16_t)~EXP_INPUTS)

#endif /* DCU_PINS_H */

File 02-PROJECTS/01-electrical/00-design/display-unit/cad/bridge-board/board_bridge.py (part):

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
def placement():
    """(ref, x, y, rotation, side). U1 turned 90 so its data pins (49-64 and 33-48) face J1 and the
    top edge, the TMDS outputs (17-32) face J2, the configuration pins (1-16) the bottom."""
    P = [("J1", 4.95, H / 2, 270, "F"),          # FH12: the mouth on the left edge
         ("U1", UX, UY, 90, "F"),
         ("J2", W - 8.0, UY, 0, "F"),            # HDMI: the mouth on the right edge
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         ("C1", 17.0, H - 8.0, 0, "F"),
         ("C2", 25.5, H - 4.5, 0, "F"),
         ("C9", W - 13.0, UY + 10.0, 0, "F"),
         ("R1", UX + 8.5, UY + 6.0, 90, "F"),     # TFADJ, pin 19 (the right side once turned)
         ("R2", UX - 4.0, UY + 10.0, 90, "F"),    # MSEN, pin 11 (the bottom once turned)
         ("R3", UX - 1.5, UY + 10.0, 90, "F"),    # PD, pin 10
         ("R4", UX + 1.0, UY + 10.0, 90, "F"),    # EDGE, pin 9
         ("JP1", UX + 4.5, UY + 13.0, 0, "F"),
         ("JP2", UX - 1.5, UY + 14.5, 0, "F"),
         ("TP1", 13.0, 4.0, 0, "F"),
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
